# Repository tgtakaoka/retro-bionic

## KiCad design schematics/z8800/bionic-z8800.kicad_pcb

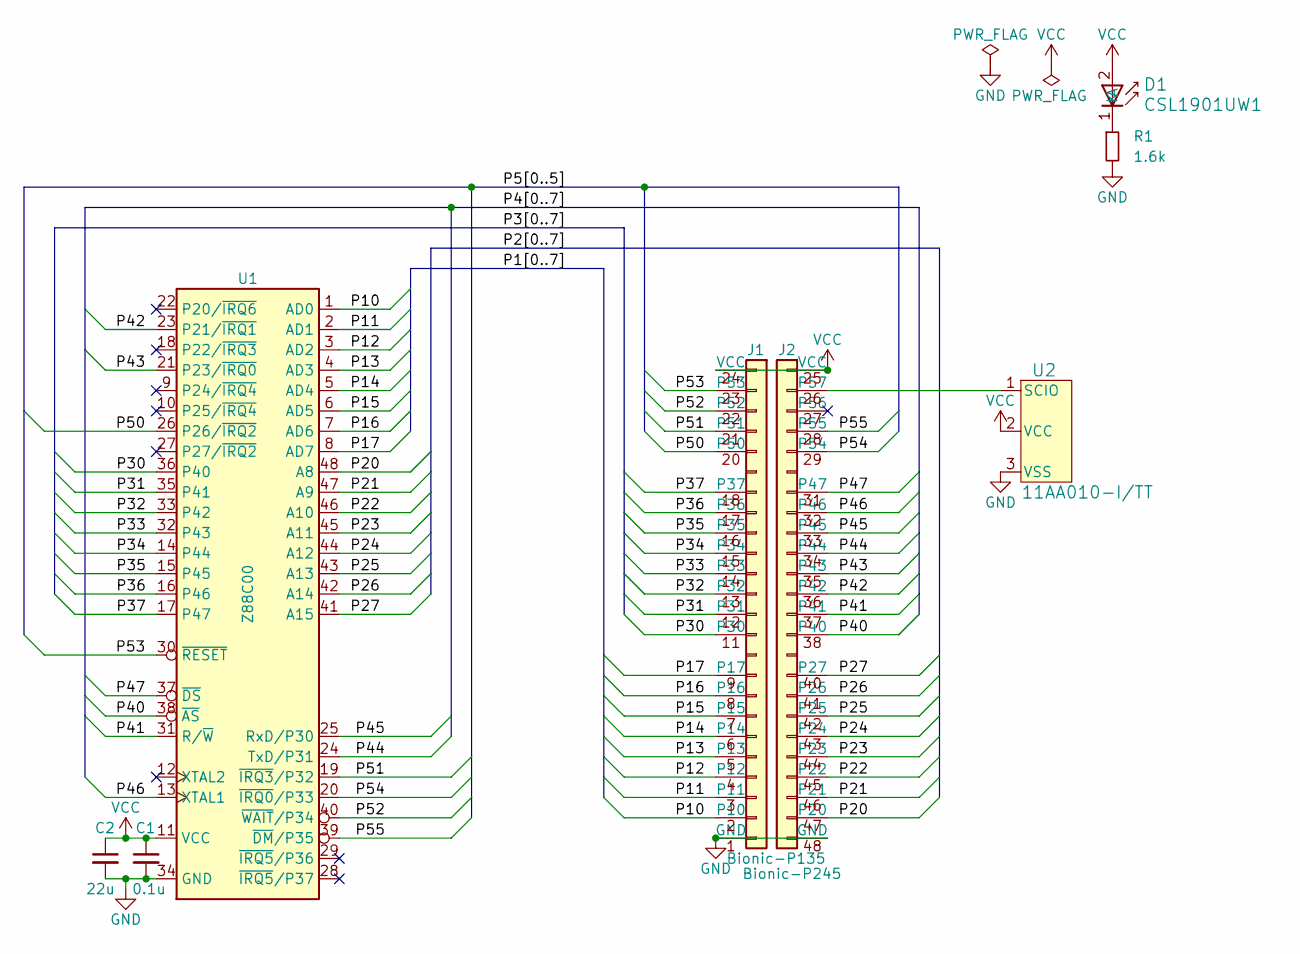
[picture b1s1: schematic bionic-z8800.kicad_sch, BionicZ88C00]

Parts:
C1: 0.1u; C_0603_1608Metric_Pad1.08x0.95mm_HandSolder
C2: 22u; C_0603_1608Metric_Pad1.08x0.95mm_HandSolder
D1: CSL1901UW1; LED_CSL1901UW1_ROM-M
J1: Bionic-P135; Bionic-P135_THT
J2: Bionic-P245; Bionic-P245_THT
R1: 1.6k; R_0603_1608Metric_Pad0.98x0.95mm_HandSolder
U1: Z88C00; DIP-48_W15.24mm_Socket
U2: 11AA010-I/TT; SOT-23_MC_MCH-M

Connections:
/P10: J1.2 (P10), U1.1 (AD0)
/P11: J1.3 (P11), U1.2 (AD1)
/P12: J1.4 (P12), U1.3 (AD2)
/P13: J1.5 (P13), U1.4 (AD3)
/P14: J1.6 (P14), U1.5 (AD4)
/P15: J1.7 (P15), U1.6 (AD5)
/P16: J1.8 (P16), U1.7 (AD6)
/P17: J1.9 (P17), U1.8 (AD7)
/P20: J2.47 (P20), U1.48 (A8)
/P21: J2.46 (P21), U1.47 (A9)
/P22: J2.45 (P22), U1.46 (A10)
/P23: J2.44 (P23), U1.45 (A11)
/P24: J2.43 (P24), U1.44 (A12)
/P25: J2.42 (P25), U1.43 (A13)
/P26: J2.41 (P26), U1.42 (A14)
/P27: J2.40 (P27), U1.41 (A15)
/P30: J1.11 (P30), U1.36 (P40)
/P31: J1.12 (P31), U1.35 (P41)
/P32: J1.13 (P32), U1.33 (P42)
/P33: J1.14 (P33), U1.32 (P43)
/P34: J1.15 (P34), U1.14 (P44)
/P35: J1.16 (P35), U1.15 (P45)
/P36: J1.17 (P36), U1.16 (P46)
/P37: J1.18 (P37), U1.17 (P47)
/P40: J2.38 (P40), U1.38 (~AS)
/P41: J2.37 (P41), U1.31 (R/~W)
/P42: J2.36 (P42), U1.23 (P21/~IRQ1)
/P43: J2.35 (P43), U1.21 (P23/~IRQ0)
/P44: J2.34 (P44), U1.24 (TxD/P31)
/P45: J2.33 (P45), U1.25 (RxD/P30)
/P46: J2.32 (P46), U1.13 (XTAL1)
/P47: J2.31 (P47), U1.37 (~DS)
/P50: J1.20 (P50), U1.26 (P26/~IRQ2)
/P51: J1.21 (P51), U1.19 (~IRQ3/P32)
/P52: J1.22 (P52), U1.40 (~WAIT/P34)
/P53: J1.23 (P53), U1.30 (~RESET)
/P54: J2.29 (P54), U1.20 (~IRQ0/P33)
/P55: J2.28 (P55), U1.39 (~DM/P35)
GND: C1.2, C2.2, J1.1 (GND), J2.48 (GND), R1.2, U1.34 (GND), U2.3 (VSS)
unnamed: D1.1 (K), R1.1
unnamed: J2.26 (P57), U2.1 (SCIO)
VCC: C1.1, C2.1, D1.2 (A), J1.24 (VCC), J2.25 (VCC), U1.11 (VCC), U2.2 (VCC)

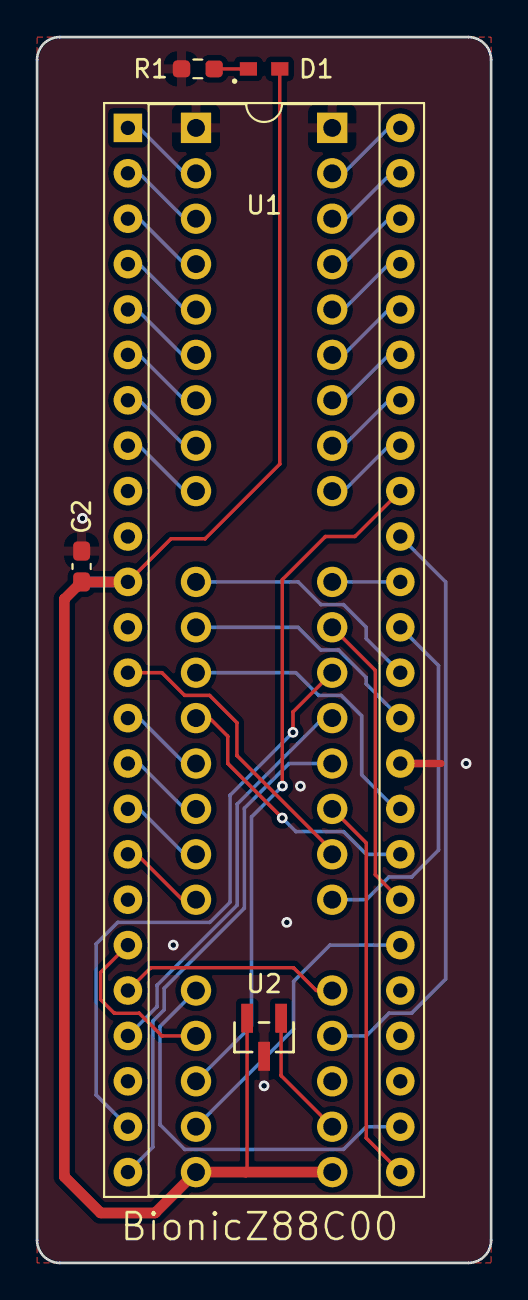
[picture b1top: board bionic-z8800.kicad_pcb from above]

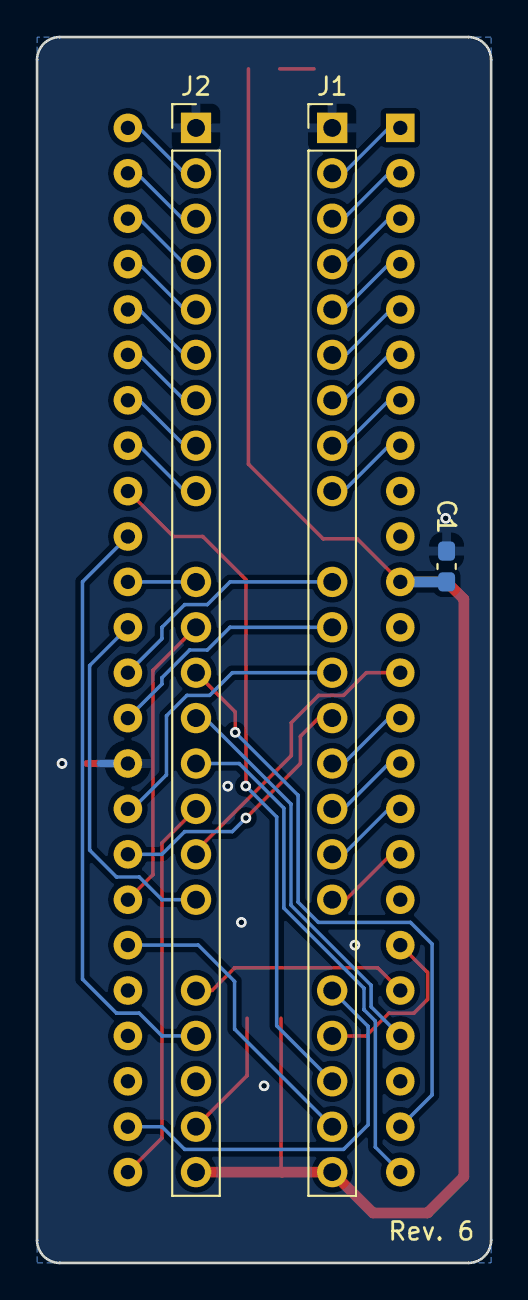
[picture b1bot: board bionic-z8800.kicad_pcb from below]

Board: 2 copper layers, 25.4 x 68.6 mm, 8 parts (3 on the bottom side), 42 nets.
